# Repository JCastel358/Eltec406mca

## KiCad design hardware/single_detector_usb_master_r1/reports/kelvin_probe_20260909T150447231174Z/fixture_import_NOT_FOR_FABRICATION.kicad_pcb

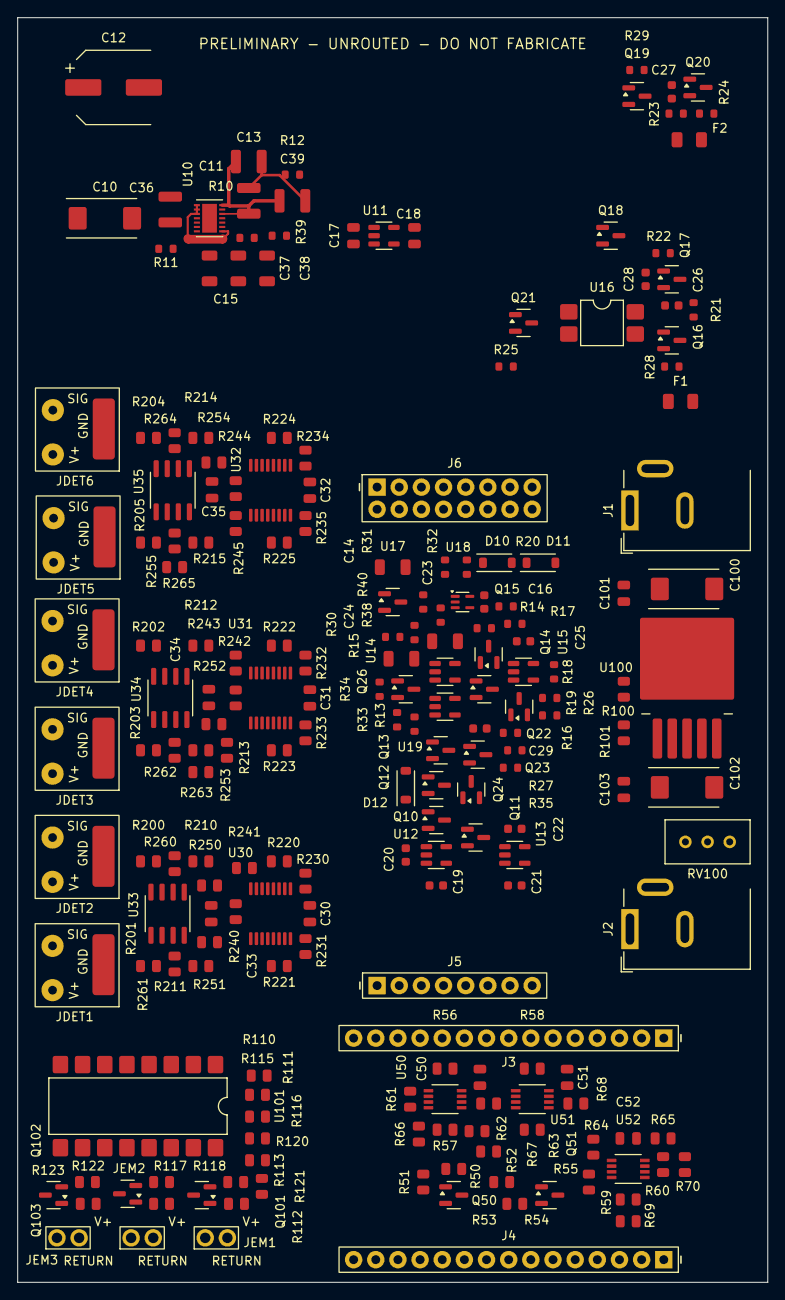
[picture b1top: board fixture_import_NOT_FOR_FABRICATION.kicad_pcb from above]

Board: 4 copper layers, 86.0 x 145.0 mm, 206 parts (0 on the bottom side), 128 nets.

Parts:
C10: 22uF 25V tantalum +/-10%; CP_EIA-7343-31_Kemet-D
C11, C13, C36, C39: 22uF 25V X7R +/-10%; C_1210_3225Metric
C12: 820uF 6.3V polymer +/-20%; CP_Elec_8x11.9
C14, C23, C24: 100nF 5% C0G; C_1206_3216Metric
C15, C37, C38: 100nF 50V 5% C0G; C_1206_3216Metric
C16, C19, C21, C25, C26, C27, C28, C29: 100nF 50V X7R; C_0603_1608Metric
C17, C18: 4.7uF 25V X7R; C_0805_2012Metric
C20, C22: 10nF 5% C0G; C_0603_1608Metric
C30, C31, C32, C33, C34, C35, C50, C51, C52: 100nF 50V X7R; C_0805_2012Metric
C100, C102: 22uF 25V 10% TPS; CP_EIA-7343-31_Kemet-D
C101, C103: 100nF 50V X7R 10%; C_0805_2012Metric
D10, D11: 1N4148W; D_SOD-123
D12: BZT52C6V8GW; D_SOD-123
F1: 1A Slo-Blo; Fuse_1206_3216Metric
F2: 1.5A Slo-Blo; Fuse_1206_3216Metric
J1, J2: GCT DCJ200-10-A / customer installed; BarrelJack_GCT_DCJ200_10_A
J3: 1x15 female socket - row A; Socket_Kinghelm_1x15_P2.54_H8.5
J4: 1x15 female socket - row B; Socket_Kinghelm_1x15_P2.54_H8.5
J5: 1x8 female ADC digital socket; Socket_Kinghelm_1x08_P2.54_H8.5
J6: 2x8 female ADC analog socket; Socket_FG_2x08_P2.54_H8.5
JDET1, JDET3, JDET5: TEST; Detector_Wire_Lands
JDET2, JDET4, JDET6: REFERENCE; Detector_Wire_Lands
JEM1: EMITTER 1; Emitter_Wire_Lands
JEM2: EMITTER 2; Emitter_Wire_Lands
JEM3: EMITTER 3; Emitter_Wire_Lands
Q10, Q11, Q23, Q24, Q26: AO3414; SOT-23
Q12, Q13, Q14, Q15, Q18, Q21: 2N7002LT1G; SOT-23
Q16, Q17, Q19, Q20: AO3401A; SOT-23
Q22, Q101, Q102, Q103: AO3400A; SOT-23
Q50, Q51: MMBT3904LT1G; SOT-23
R10: 51.1k 0.1% 10ppm/K; R_0603_1608Metric
R11: 300 0.1%; R_0603_1608Metric
R12, R20: 4.7k 1%; R_0603_1608Metric
R13, R18, R21, R23, R33, R38: 10k 1%; R_0603_1608Metric
R14, R15, R27, R28, R29, R34, R35: 100k 1%; R_0603_1608Metric
R16, R17, R22, R24: 1k 1%; R_0603_1608Metric
R19: 0; R_0603_1608Metric
R25: 390 1%; R_0603_1608Metric
R26: 100 1%; R_0603_1608Metric
R30: 1.5k 1%; R_0603_1608Metric
R31: 221 0.1% 25ppm/K; R_0603_1608Metric
R32: 1.00k 0.1% 25ppm/K; R_0603_1608Metric
R39: 698 0.1% 10ppm/K; R_0603_1608Metric
R40: 150 1%; R_0603_1608Metric
R50, R52, R53, R55, R61, R62, R63, R64, R65, R66, R67, R68, R69, R70: 10k; R_0805_2012Metric
R51, R54: 100k; R_0805_2012Metric
R56, R57, R58, R59, R60: 33; R_0805_2012Metric
R100: 210R 1% 0.125W; R_0805_2012Metric
R101: 7R5 1% 0.125W; R_0805_2012Metric
R110, R115, R120: 240R 1% 0.125W; R_0805_2012Metric
R111, R116, R121: 100k 1% 0.125W; R_0805_2012Metric
R112, R117, R122: 100R 1% 0.125W; R_0805_2012Metric
R113, R118, R123: 10k 1% 0.125W; R_0805_2012Metric
R200, R201, R202, R203, R204, R205: 100k 1%; R_0805_2012Metric
R210, R211, R212, R213, R214, R215: 10k 1%; R_0805_2012Metric
R220, R221, R222, R223, R224, R225, R250, R251, R252, R253, R254, R255: 499R 0.1%; R_0805_2012Metric
R230, R231, R232, R233, R234, R235: 220R 1%; R_0805_2012Metric
R240, R241, R242, R243, R244, R245, R260, R261, R262, R263, R264, R265: 33k 0.1%; R_0805_2012Metric
RV100: 1k 25-turn 0.5W; Potentiometer_Bourns_3296W_Vertical
U10: LT3041ADE#TRPBF; DFN-14-1EP_3x4mm_P0.5mm_EP1.7x3.3mm
U11: AP2112K-3.3TRG1; SOT-23-5
U12: TPS3840PL42DBVR; SOT-23-5
U13: TPS3840PL30DBVR; SOT-23-5
U14: TPS3840PL34DBVR; SOT-23-5
U15: SN74LVC1G14DBVR; SOT-23-5
U16: LTV-817S-TA1-B; SMDIP-4_W7.62mm
U17: LM4050AIM3-4.1/NOPB; SOT-23
U18: TLV3601DCKR; SOT-353_SC-70-5
U19: SN74LVC1G132DBVR; SOT-23-5
U30, U31, U32: ADG4613BRUZ; TSSOP-16_4.4x5mm_P0.65mm
U33, U34, U35: OPA2325IDR; SOIC-8_3.9x4.9mm_P1.27mm
U50, U51, U52: SN74LVC2G125DCTR; TI_DCT0008A_SSOP8
U100: LT1963AEQ#PBF; TO-263-5_TabPin3
U101: LTV-847S; SMDIP-16_W9.53mm

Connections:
ADC_5V_HELD: C11.1, C12.1, C13.1, C16.1, C17.1, C23.1, C30.1, C31.1, C32.1, C33.1, C34.1, C35.1, C39.1, D11.2, J5.1, R12.1, R17.1, R30.1, R31.1, R38.1, U10.12, U10.13, U10.14, U11.1, U11.3, U18.5, U30.13, U31.13, U32.13, U33.8, U34.8, U35.8
ADC_AIN0: J6.1, R240.1, U30.2, U30.15
ADC_AIN1: J6.3, R241.1, U30.7, U30.10
ADC_AIN2: J6.5, R242.1, U31.2, U31.15
ADC_AIN3: J6.7, R243.1, U31.7, U31.10
ADC_AIN4: J6.9, R244.1, U32.2, U32.15
ADC_AIN5: J6.11, R245.1, U32.7, U32.10
ADC_COMPARATOR_GOOD: R16.1, U18.1
ADC_CS_DRV: R58.1, U51.6
ADC_CS_N: J5.7, R58.2, R68.1
ADC_DRDY_N: J5.6, R65.1, U52.5
ADC_IF_OE_N: Q50.3, R52.2, U50.1, U50.7, U51.1
ADC_IO_3V3: C18.1, C25.1, C50.1, C51.1, R20.1, R25.1, R52.1, R68.2, U11.5, U15.5, U50.8, U51.7, U51.8
ADC_LDO_ILIM: R11.1, U10.7
ADC_LDO_SET: C15.1, C37.1, C38.1, R10.1, U10.9
ADC_LDO_SET_RETURN: R10.2, R39.1
ADC_MISO: J5.5, R64.1, U52.2
ADC_MOSI: J5.4, R57.2, R67.1
ADC_MOSI_DRV: R57.1, U50.3
ADC_OE_BASE: Q50.1, R50.2, R51.1
ADC_PDWN_N: J5.8, Q15.3, R20.2
ADC_RAIL_SENSE: R31.2, R32.1, U18.3
ADC_READY_RAW: Q14.1, Q18.1, Q21.1, Q23.3, Q24.3, R16.2, R35.1, U19.1
ADC_REG_EN: Q12.3, R14.2, U10.5
ADC_SCLK: J5.3, R56.2, R66.1
ADC_SCLK_DRV: R56.1, U50.6
ADC_SUP_CT: C24.1, U14.5
ADC_SUP_MR_N: Q13.3, R15.2, U14.4
AMP_FB0: R250.2, R260.1, U33.2
AMP_FB1: R251.2, R261.1, U33.6
AMP_FB2: R252.2, R262.1, U34.2
AMP_FB3: R253.2, R263.1, U34.6
AMP_FB4: R254.2, R264.1, U35.2
AMP_FB5: R255.2, R265.1, U35.6
AMP_IN0: R210.2, U33.3
AMP_IN1: R211.2, U33.5
AMP_IN2: R212.2, U34.3
AMP_IN3: R213.2, U34.5
AMP_IN4: R214.2, U35.3
AMP_IN5: R215.2, U35.5
AMP_OUT0: R220.1, R250.1, U33.1
AMP_OUT1: R221.1, R251.1, U33.7
AMP_OUT2: R222.1, R252.1, U34.1
AMP_OUT3: R223.1, R253.1, U34.7
AMP_OUT4: R224.1, R254.1, U35.1
AMP_OUT5: R225.1, R255.1, U35.7
AMP_SERIES0: R220.2, U30.14
AMP_SERIES1: R221.2, U30.11
AMP_SERIES2: R222.2, U31.14
AMP_SERIES3: R223.2, U31.11
AMP_SERIES4: R224.2, U32.14
AMP_SERIES5: R225.2, U32.11
CLAMP_GND0: R230.1, U30.3
CLAMP_GND1: R231.1, U30.6
CLAMP_GND2: R232.1, U31.3
CLAMP_GND3: R233.1, U31.6
CLAMP_GND4: R234.1, U32.3
CLAMP_GND5: R235.1, U32.6
DET_BAT_FUSED: F1.2, Q16.3
DET_BAT_PROTECTED: C10.1, C26.2, C36.1, D10.2, Q16.2, Q17.2, R14.1, R21.2, U10.1, U10.2, U10.3, U10.8
DET_BAT_RAW: F1.1, J1.1
DET_MASTER_GATE: C26.1, Q17.1, R21.1, R22.1
DET_MASTER_SINK: Q18.3, R22.2
DET_RPOL_GATE: Q16.1, R28.1
EMIT1_LOW: JEM1.2, Q101.3
EMIT2_LOW: JEM2.2, Q102.3
EMIT3_LOW: JEM3.2, Q103.3
EM_ADJ: R100.1, R101.2, U100.5
EM_BAT_FUSED: F2.2, Q19.3
EM_BAT_PROTECTED: C27.2, Q19.2, Q20.2, R23.2
EM_BAT_RAW: F2.1, J2.1
EM_BAT_SW: C100.1, C101.1, Q20.3, U100.1, U100.2, U101.12, U101.14, U101.16
EM_GATE1: Q101.1, R112.2, R113.1
EM_GATE1_DRIVE: R112.1, U101.15
EM_GATE2: Q102.1, R117.2, R118.1
EM_GATE2_DRIVE: R117.1, U101.13
EM_GATE3: Q103.1, R122.2, R123.1
EM_GATE3_DRIVE: R122.1, U101.11
EM_GND: C100.2, C101.2, C102.2, C103.2, J2.2, Q101.2, Q102.2, Q103.2, R29.2, R100.2, R113.2, R118.2, R123.2, U16.3, U100.3
EM_LED1_A: R110.2, U101.1
EM_LED2_A: R115.2, U101.3
EM_LED3_A: R120.2, U101.5
EM_LED_ENABLE_GATE: Q22.1, R26.2, R27.1
EM_LED_RETURN: Q22.3, U101.2, U101.4, U101.6
EM_MASTER_GATE: C27.1, Q20.1, R23.1, R24.1
EM_MASTER_LED_A: R25.2, U16.1
EM_MASTER_LED_K: Q21.3, U16.2
EM_OPTO_C: R24.2, U16.4
EM_REG: C102.1, C103.1, JEM1.1, JEM2.1, JEM3.1, RV100.1, RV100.2, U100.4
EM_RPOL_GATE: Q19.1, R29.1
EM_TRIM_TOP: R101.1, RV100.3
ENABLE_AND_MID: Q10.2, Q11.3
ESP_3V3: C21.1, C29.1, C52.1, J3.1, R55.1, R63.2, U13.2, U13.4, U19.5, U52.8
ESP_CS_N: J3.8, R63.1, U51.2
ESP_DRDY: J3.5, R60.2, R70.1
ESP_DRDY_DRV: R60.1, U52.3
ESP_EMIT1: J4.9, R110.1, R111.1
ESP_EMIT2: J4.8, R115.1, R116.1
ESP_EMIT3: J4.7, R120.1, R121.1
ESP_IF_OE_N: Q51.3, R55.2, U52.1, U52.7
ESP_MISO: J3.10, R59.2, R69.1
ESP_MISO_DRV: R59.1, U52.6
ESP_MOSI: J3.15, R62.1, U50.5
ESP_OE_BASE: Q51.1, R53.2, R54.1
ESP_POWER_NOT_READY: J4.11, R33.1, U19.4
ESP_SCLK: J3.9, R61.1, U50.2
ESP_SUP_CT: C22.1, U13.5
ESP_VALID_RAW: Q11.1, U13.1
GND: C10.2, C11.2, C12.2, C13.2, C14.2, C15.2, C16.2, C17.2, C18.2, C19.2, C20.2, C21.2, C22.2, C24.2, C25.2, C28.2, C29.2, C30.2, C31.2, C32.2, C33.2, C34.2, C35.2, C36.2, C37.2, C38.2, C39.2, C50.2, C51.2, C52.2, D12.2, J1.2, J3.2, J4.2, J5.2, J6.2, J6.4, J6.6, J6.8, J6.10, J6.12, J6.13, J6.14, J6.15, J6.16, JDET1.3, JDET2.3, JDET3.3, JDET4.3, JDET5.3, JDET6.3, Q11.2, Q12.2, Q13.2, Q14.2, Q15.2, Q18.2, Q21.2, Q22.2, Q23.2, Q24.2, Q26.2, Q50.2, Q51.2, R11.2, R12.2, R18.2, R27.2, R28.2, R32.2, R33.2, R34.2, R35.2, R39.2, R51.2, R54.2, R61.2, R62.2, R64.2, R65.2, R66.2, R67.2, R69.2, R70.2, R111.2, R116.2, R121.2, R200.2, R201.2, R202.2, R203.2, R204.2, R205.2, R230.2, R231.2, R232.2, R233.2, R234.2, R235.2, R240.2, R241.2, R242.2, R243.2, R244.2, R245.2, R260.2, R261.2, R262.2, R263.2, R264.2, R265.2, U10.10, U10.11, U10.15, U11.2, U12.3, U13.3, U14.3, U15.3, U17.2, U17.3, U18.2, U19.3, U30.4, U30.5, U31.4, U31.5, U32.4, U32.5, U33.4, U34.4, U35.4, U50.4, U51.4, U51.5, U52.4
ISOLATE_H: Q14.3, Q15.1, R17.2, U15.2, U30.1, U30.8, U30.9, U30.16, U31.1, U31.8, U31.9, U31.16, U32.1, U32.8, U32.9, U32.16
MASTER_PERMIT: R18.1, R19.1, R26.1, U15.4
OFF_BIAS_RAIL: D10.1, D11.1, R13.1
POWER_OFF_NODE: D12.1, Q10.3, Q12.1, Q13.1, Q24.1, R13.2
PWR_REF_4V096: C14.1, R15.1, R30.2, U14.2, U17.1, U18.4
REF_CLAMP_RELEASE: Q26.3, R40.2
REF_NOT_READY: C23.2, Q23.1, R38.2, R40.1
REF_READY_RAW: Q26.1, R34.1, U14.1, U19.2
SENSOR0: JDET1.2, R200.1, R210.1
SENSOR1: JDET2.2, R201.1, R211.1
SENSOR2: JDET3.2, R202.1, R212.1
SENSOR3: JDET4.2, R203.1, R213.1
SENSOR4: JDET5.2, R204.1, R214.1
SENSOR5: JDET6.2, R205.1, R215.1
SENSOR_BAT_SW: C28.1, JDET1.1, JDET2.1, JDET3.1, JDET4.1, JDET5.1, JDET6.1, Q17.3
SPI_PERMIT: R19.2, R50.1, R53.1
USB_PRESENT_5V: C19.1, J4.1, U12.2, U12.4
USB_SUP_CT: C20.1, U12.5
USB_VALID_RAW: Q10.1, U12.1
